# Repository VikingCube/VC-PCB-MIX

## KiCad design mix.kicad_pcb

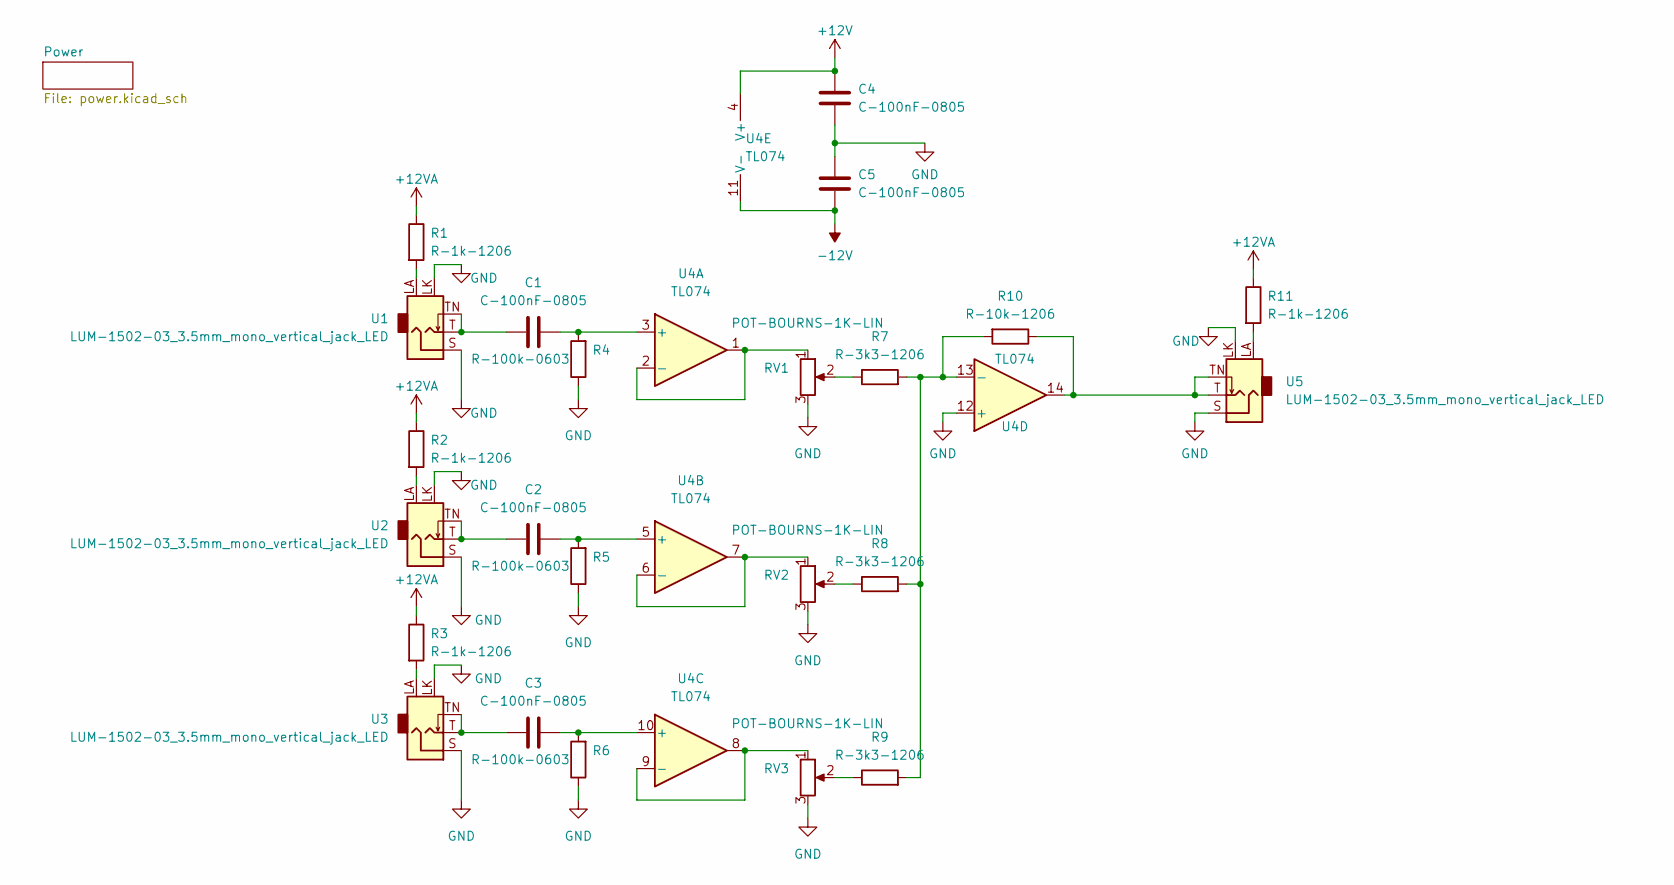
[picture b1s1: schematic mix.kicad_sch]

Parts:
C1, C2, C3, C4, C5: C-100nF-0805; C_0805_2012Metric_Pad1.18x1.45mm_HandSolder
R1, R2, R3, R11: R-1k-1206; R_1206_3216Metric_Pad1.30x1.75mm_HandSolder; Tolerance 5%
R4, R5, R6: R-100k-0603; R_0603_1608Metric
R7, R8, R9: R-3k3-1206; R_1206_3216Metric_Pad1.30x1.75mm_HandSolder; Tolerance 5%
R10: R-10k-1206; R_1206_3216Metric_Pad1.30x1.75mm_HandSolder
RV1, RV2, RV3: POT-BOURNS-1K-LIN; Potentiometer_Bourns_PTV09A-1_Single_Vertical
U1, U2, U3, U5: LUM-1502-03_3.5mm_mono_vertical_jack_LED; LUM 1502-03 LED
U4: TL074; SO-14_5.3x10.2mm_P1.27mm

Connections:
+12VA: R1.1, R2.1, R3.1, R11.1; also elsewhere on the board
unnamed: C1.1, U1.T, U1.TN
unnamed: C1.2, R4.2, U4.3 (+)
unnamed: C2.1, U2.T, U2.TN
unnamed: C2.2, R5.2, U4.5 (+)
unnamed: C3.1, U3.T, U3.TN
unnamed: C3.2, R6.2, U4.10 (+)
unnamed: R1.2, U1.LA
unnamed: R2.2, U2.LA
unnamed: R3.2, U3.LA
unnamed: R7.1, RV1.2
unnamed: R8.1, RV2.2
unnamed: R9.1, RV3.2
unnamed: R10.1, U4.14, U5.T, U5.TN
unnamed: R7.2, R8.2, R9.2, R10.2, U4.13 (-)
unnamed: RV1.1, U4.1, U4.2 (-)
unnamed: RV2.1, U4.6 (-), U4.7
unnamed: RV3.1, U4.8, U4.9 (-)
unnamed: R11.2, U5.LA

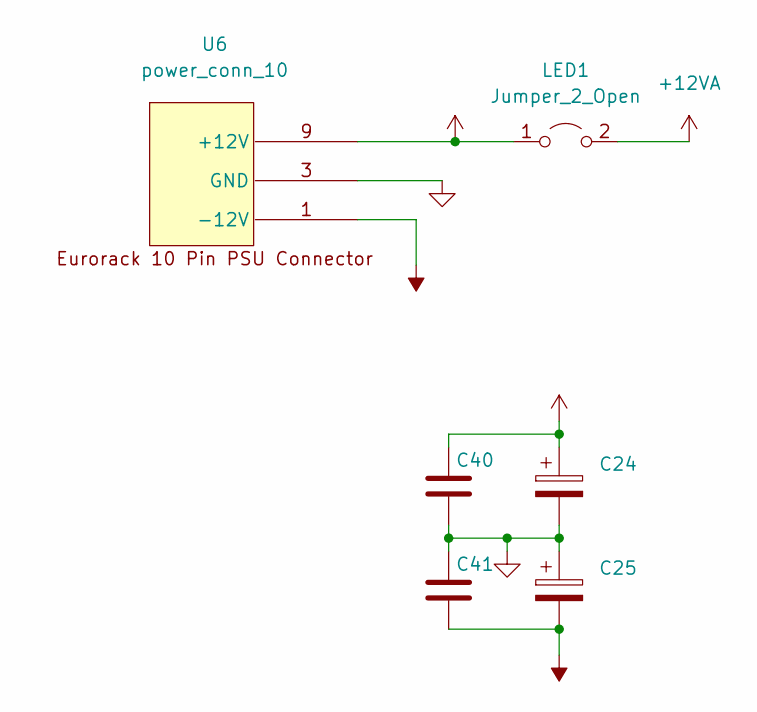
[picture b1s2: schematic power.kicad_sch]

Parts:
C24, C25, C40, C41: (no value)
LED1: Jumper_2_Open; PinHeader_1x02_P2.54mm_Vertical
U6: power_conn_10; power_10

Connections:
+12VA: LED1.2 (B); also elsewhere on the board

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
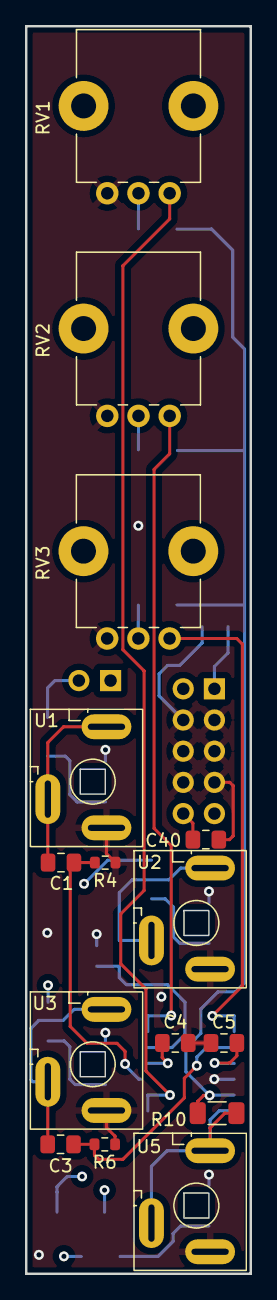
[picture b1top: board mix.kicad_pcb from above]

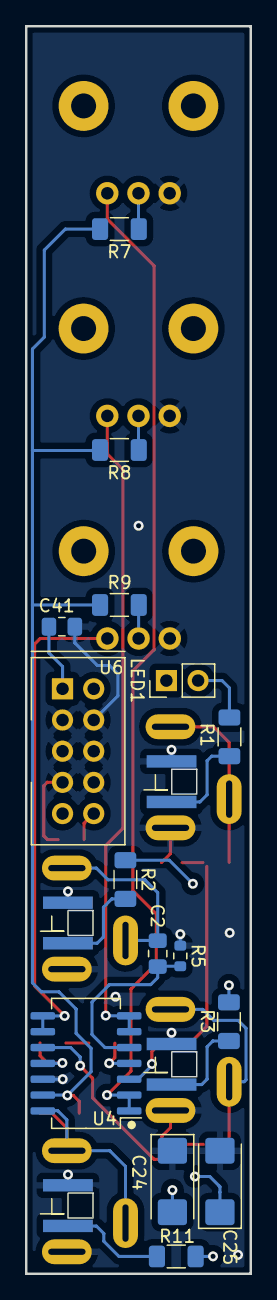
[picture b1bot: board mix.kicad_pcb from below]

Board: 4 copper layers, 18.0 x 100.0 mm, 30 parts (15 on the bottom side), 22 nets.

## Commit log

2022-12-13 first version DRC ready
